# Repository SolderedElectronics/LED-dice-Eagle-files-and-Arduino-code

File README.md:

# LED dice
## Image

[LED dice(100034)](https://e-radionica.com/en/kokica-od-leda-set-za-ucenje-lemljenja.html)

## Description and details
LED dice is simple & easy way to get into soldering. While learning to solder, you will also create unique gadget which you can carry around. Board is powered by small CR2032 battery and the brain of circuit Atmel Attiny85 microcontroller.

Feel free to bump into code! We are looking to implement sleep function for Attiny85 to save battery power.

## Repository content
This repo contains Cadsoft Eagle .sch and .brd files for LED dice PCB board. It also contains schematic in .pdf created from .sch Eagle file. 
Files have been arranged into folders for navigating between different versions of board. 
Tip: layer 200 shows top silkscreen and layer 208 should be bottom silkscreen. tParts and bParts layers are not used.
There is also a Firmware folder in which you can find Arduino code for microcontroller which is programmed to Attiny85.
In Firmware folder, you will also find v2.c file. This is code written in C, doing the same thing as Arduino version, but it was written this way so it could fit to the Attiny13(less then 1kB of Flash). 

## Docs
- [LED dice product page] (https://e-radionica.com/en/kokica-od-leda-set-za-ucenje-lemljenja.html)
- 
## Board versions
- v1.0 - inital version
- v1.1 - bottom silkscreen error fixed

## License info
This product is open-source. Yay!
For any tech questions, contact us at techsupport@e-radionica.com
If you find an Issue, please open one at GitHub. If you can improve our product, fork us. We are looking forward to it!

e-radionica.com Team.

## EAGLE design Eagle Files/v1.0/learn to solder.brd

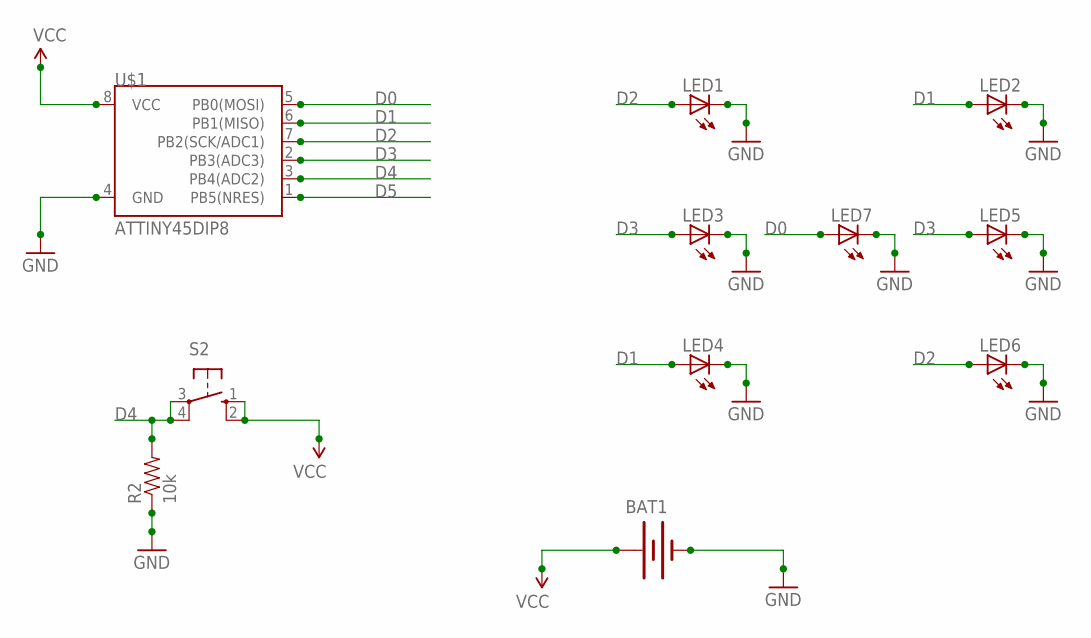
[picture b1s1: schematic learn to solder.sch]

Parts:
BAT1: BATTERY20PTH; BATTCOM_20MM_PTH
LED1, LED2, LED3, LED4, LED5, LED6, LED7: LED5MM
R2: 10k; AXIAL-0.3
S2: 40-XX; B3F-40XX
U$1: ATTINY45DIP8; DIP08

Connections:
D0: LED7.A, U$1.5 (PB0(MOSI))
D1: LED2.A, LED4.A, U$1.6 (PB1(MISO))
D2: LED1.A, LED6.A, U$1.7 (PB2(SCK/ADC1))
D3: LED3.A, LED5.A, U$1.2 (PB3(ADC3))
D4: R2.P$2 (2), S2.3, S2.4 (P1), U$1.3 (PB4(ADC2))
D5: U$1.1 (PB5(NRES))
GND: BAT1.2 (-), LED1.K (C), LED2.K (C), LED3.K (C), LED4.K (C), LED5.K (C), LED6.K (C), LED7.K (C), R2.P$1 (1), U$1.4 (GND)
VCC: BAT1.1 (+), S2.1 (S), S2.2 (S1), U$1.8 (VCC)

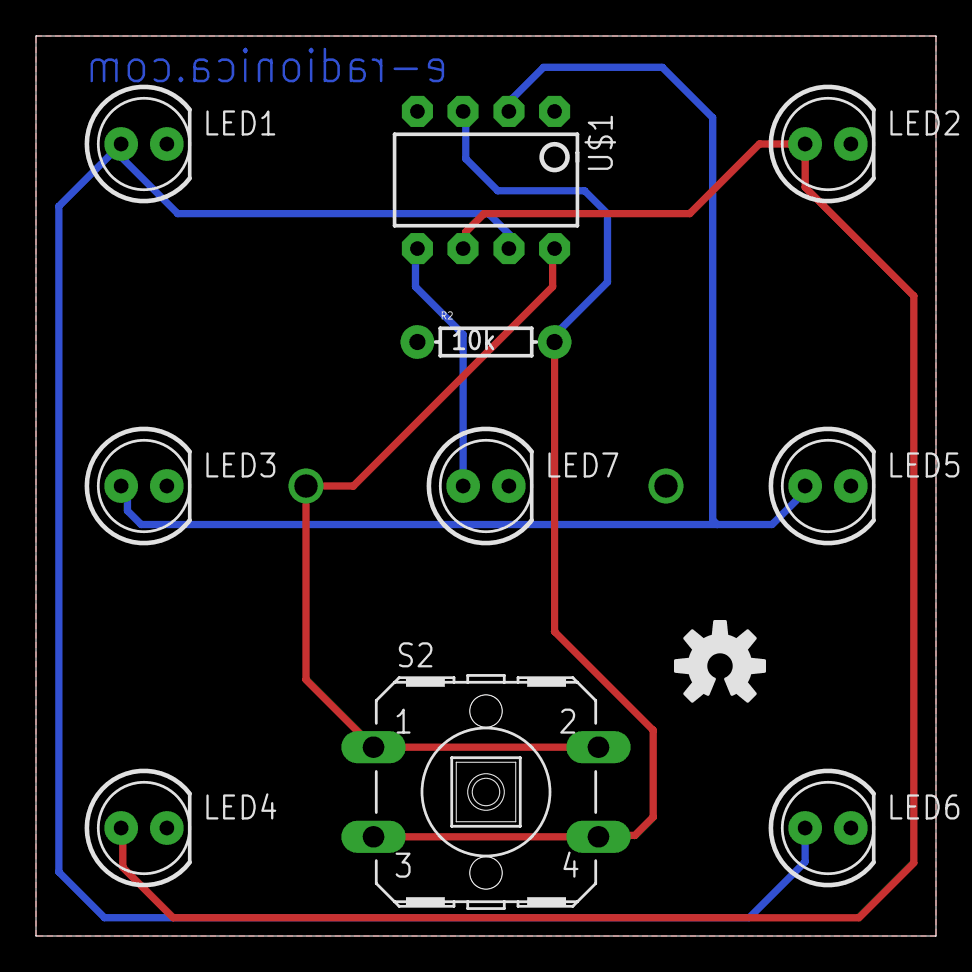
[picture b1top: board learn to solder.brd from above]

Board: 2 copper layers, 50.0 x 50.0 mm, 14 parts (1 on the bottom side), 7 nets.

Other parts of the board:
U$2: UTICNICA6MM
U$3: OSHW-LOGO-M
U$4: MADE-IN-CROATIA

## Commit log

2016-08-17 Initial upload
2016-11-25 Adding under 1kB version of code
2018-11-26 README update

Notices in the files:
parts and their libraries:
SparkFun: Licensing: CC v3.0 Share-Alike You are welcome to use this library for commercial purposes.
